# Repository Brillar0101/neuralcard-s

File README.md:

# NeuralCard

A business card that runs a neural network.

> This is the sponsorship build, a fork of
> [NeuralCard](https://github.com/Brillar0101/NeuralCard) prepared for assembly by
> PCBWay. The BOM has been rewritten from JLCPCB and LCSC part codes into
> manufacturer part numbers PCBWay can quote, with approved alternates where a swap
> is safe and do-not-substitute rules where it is not. Every part in the schematic
> and the board now carries `Alt MPN`, `Alt Mfr`, and `Sourcing` fields alongside
> the existing MPN. See [`docs/SOURCING.md`](docs/SOURCING.md) for the reasoning and
> [`fab/BOM_PCBWay.csv`](fab/BOM_PCBWay.csv) for the order-ready BOM. No copper
> changed, and DRC and ERC still pass clean.

It is a credit-card-sized PCB, 85.6 by 54 mm, carrying an ESP32-S3, a 6-axis
IMU, and 24 LEDs laid out as the network it actually runs: 6 input neurons,
8 hidden, 10 output. You hold the card, draw a digit in the air, and the LEDs
light with the real activations as inference runs. Brightest output neuron
wins.

The front artwork is the network diagram. The synapse lines are drawn at three
stroke weights, the way a trained model's weights differ. There is also an NFC
tag with a coil antenna etched into the copper, so tapping a phone opens
[princetekki.com/card](https://www.princetekki.com/card) and offers a vCard.
That works with a dead battery, or no battery at all, because the phone's own
field powers the tag.

## Repository layout

| Path | What's in it |
|---|---|
| `hardware/` | KiCad 10 project: schematic, board, custom symbol and footprint libraries, 3D models |
| `fab/` | Manufacturing outputs: gerber zip, drill files, pick-and-place, and two BOMs: `BOM_PCBWay.csv` (MPN-based, for this build) and `BOM_JLCPCB.csv` (upstream, LCSC codes) |
| `firmware/` | ESP-IDF project. Charlieplex driver, IMU driver, gesture recorder. Builds today. |
| `docs/` | Design rationale, component sourcing, datasheet findings, DRC history, audits, FAQ |
| `render/` | The board renders used above |
| `CHANGELOG.md` | Revision history, newest first |

Start with [`docs/DESIGN.md`](docs/DESIGN.md) for why the board is shaped the
way it is, [`docs/FAQ.md`](docs/FAQ.md) for the questions people actually ask,
and [`docs/drc/README.md`](docs/drc/README.md) for the verification trail.

## Hardware

An ESP32-S3-WROOM-1-N8R2 does the thinking and runs the inference. An
LSM6DS3TR-C accelerometer and gyro sits on I2C, and its six axes map one to one
onto the six input neurons. The 24 red LEDs are charlieplexed across 6 GPIO
with software PWM for the glow.

For the business-card half there is an ST25DV04K dynamic NFC tag with a 9-turn
coil in the copper, tuned by a single external cap (C12) against the chip's
internal capacitance.

USB-C arrived in v2.3. The S3 has native USB, so a plain cable flashes the
board and gives a serial console without an adapter. A USBLC6-2SC6 protects the
data pair.

Power comes from either a CR2032 through a real slide switch (SW3) or USB 5 V
through an ME6211 LDO. A P-FET (Q1) disconnects the cell whenever USB is
present, so the board can never try to charge a cell that is not rechargeable.

Two layers, ground poured on both sides and stitched. Every net is one
connected cluster.

## How it's wired

Power first. Two sources that can never fight each other.

```mermaid
flowchart LR
    USB["USB-C · J2<br/>5 V VBUS"] --> LDO["U3 · ME6211<br/>3.3 V LDO"]
    BT1["BT1<br/>CR2032 · 3.0 V"] -->|VBAT| SW3{{"SW3 · MSK12C02<br/>SPDT slide"}}
    SW3 -->|"ON"| Q1{{"Q1 · AO3401A<br/>P-FET isolation"}}
    SW3 -.->|"OFF"| NC(["open throw"])
    LDO --> RAIL[["+3V3 rail"]]
    LDO -.->|"VBUS present<br/>gates the cell off"| Q1
    Q1 --> RAIL
    RAIL --> U1["ESP32-S3"]
    RAIL --> U2["LSM6DS3TR-C"]
    RAIL --> U4["ST25DV04K"]
    RAIL --> LEDS["24 LEDs<br/>charlieplexed"]

    classDef src fill:#F0AB00,stroke:#795600,color:#151515
    classDef sw fill:#0066CC,stroke:#003366,color:#FFFFFF
    classDef rail fill:#009596,stroke:#005F60,color:#FFFFFF
    classDef load fill:#F0F0F0,stroke:#8A8D90,color:#151515
    classDef off fill:#FFFFFF,stroke:#C9190B,color:#C9190B,stroke-dasharray:4 3
    class USB,BT1 src
    class SW3,Q1,LDO sw
    class RAIL rail
    class U1,U2,U4,LEDS load
    class NC off
```

Then data. USB-C carries both power and programming. NFC is independent of
both and needs no power of its own.

```mermaid
flowchart LR
    HOST(["laptop"]) -->|"USB-C · D+/D-"| ESD["U5 · USBLC6<br/>ESD array"]
    ESD -->|"native USB-Serial-JTAG"| U1["ESP32-S3"]
    U1 <-->|I2C| U2["IMU"]
    U1 <-->|I2C| U4["NFC tag"]
    U2 -.->|"motion interrupt"| U1
    U4 -.->|"field-detect GPO"| U1
    PHONE(["phone"]) -.->|"13.56 MHz field<br/>powers the tag"| U4
    U1 --> LEDS["24 LEDs"]

    classDef ext fill:#F0AB00,stroke:#795600,color:#151515
    classDef chip fill:#0066CC,stroke:#003366,color:#FFFFFF
    classDef out fill:#3E8635,stroke:#1F4D19,color:#FFFFFF
    class HOST,PHONE ext
    class ESD,U1,U2,U4 chip
    class LEDS out
```

And inference. The six IMU axes feed the six input neurons, and the LEDs at
each node light with the real activations as the network runs.

```mermaid
flowchart LR
    IMU["LSM6DS3TR-C<br/>ax ay az · gx gy gz"] --> IN["INPUT<br/><b>6 neurons</b>"]
    IN --> HID["HIDDEN<br/><b>8 neurons</b>"]
    HID --> OUT["OUTPUT<br/><b>10 neurons</b><br/>digits 0-9"]
    OUT --> GUESS(["brightest neuron<br/>= the guess"])

    classDef sensor fill:#F0AB00,stroke:#795600,color:#151515
    classDef layer fill:#0066CC,stroke:#003366,color:#FFFFFF
    classDef out fill:#5752D1,stroke:#2A265F,color:#FFFFFF
    classDef result fill:#3E8635,stroke:#1F4D19,color:#FFFFFF
    class IMU sensor
    class IN,HID layer
    class OUT out
    class GUESS result
```

All 24 LEDs run from 6 GPIO by charlieplexing. That is why there are 6
current-limiting resistors rather than 24, and why the display works on a coin
cell at all: only one LED is ever actually lit.

## Firmware

`firmware/` is an ESP-IDF project that builds today. It has the charlieplex
driver, with the LED-to-pin mapping extracted from the board netlist rather
than guessed, the LSM6DS3 driver, and a motion-triggered gesture recorder that
prints labelled CSV over the USB-C console. That recorder is how you build a
training set.

```
cd firmware && idf.py set-target esp32s3 && idf.py build && idf.py flash monitor
```

The neural network itself is deliberately not in the repo yet: it has to be
trained on gestures recorded from real hands, which needs assembled boards.
See [`firmware/README.md`](firmware/README.md).

## Ordering

Everything a fab needs is in `fab/`: `NeuralCard_gerbers.zip` (gerbers +
drill), `NeuralCard-cpl.csv` (placements), and a BOM. Use
`BOM_PCBWay.csv` for this build, which carries manufacturer part numbers,
approved alternates, and per-line substitution rules. `BOM_JLCPCB.csv` is the
upstream file and is keyed to LCSC codes instead.

Build spec: 2 layers, 1.6 mm thickness, green soldermask, HASL. That is the
cheap prototype configuration, currently about $2 for five boards.

Two finish options are worth knowing about if you ever make a batch to hand
out. At 0.8 mm the board feels like a card instead of a circuit board. With
ENIG, the hairline under the name comes out gold, since it is a mask opening
over the ground pour and plates with whatever finish you pick. Both cost more.
Neither changes the gerbers, so they are order-time choices.

**Two build routes:**

Hand assembly means ordering bare boards plus a solder-paste stencil and
buying parts from LCSC. It is the cheapest route, and the stencil is what makes
the LGA-14 IMU tractable with hot air.

Factory assembly means turnkey PCBA on both sides. It adds roughly $100 of fixed
setup and feeder cost at a typical prototype house, so it only pays off around 30
boards or more. This build is being assembled by PCBWay under sponsorship, so see
[`docs/SOURCING.md`](docs/SOURCING.md) for how the parts are actually bought.

Two BOM notes. C12, the NFC tuning cap, ships as 68 pF and should be retuned
against the coil once it exists. Read range is the practical test. The NFC chip
is ST25DV04KC-IE6S3, which is the active part. The older ST25DV04K-IER6S3 is
marked not recommended for new designs but is still widely stocked, and it is
listed as the approved fallback: same package, same pinout, same function.

## Status

The hardware is done and verified at v2.3.1: DRC reports 0 violations and 0
unconnected, ERC is clean, every net is a single connected cluster, and the
footprints have been checked against manufacturer datasheets. It has never been
fabricated. These files would produce the first physical boards.

The firmware scaffold builds. Drivers and gesture capture work. The trained
model is the remaining piece, and it needs assembled boards before it can
exist.

So today the card is a very elaborate NFC business card, and that part works
the moment the tag is programmed.

## License

CERN-OHL-P v2. See [LICENSE](LICENSE). Do whatever you want with it,
attribution appreciated.

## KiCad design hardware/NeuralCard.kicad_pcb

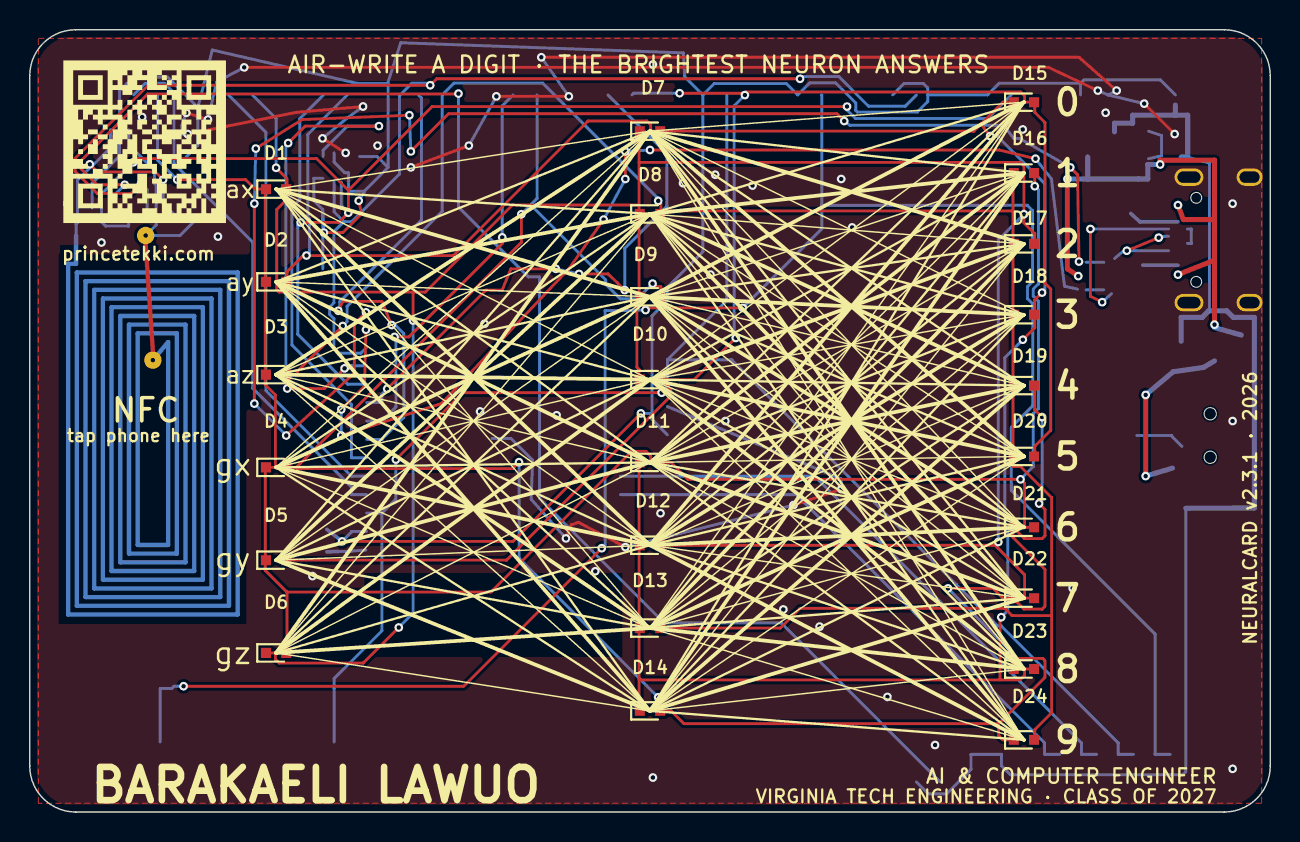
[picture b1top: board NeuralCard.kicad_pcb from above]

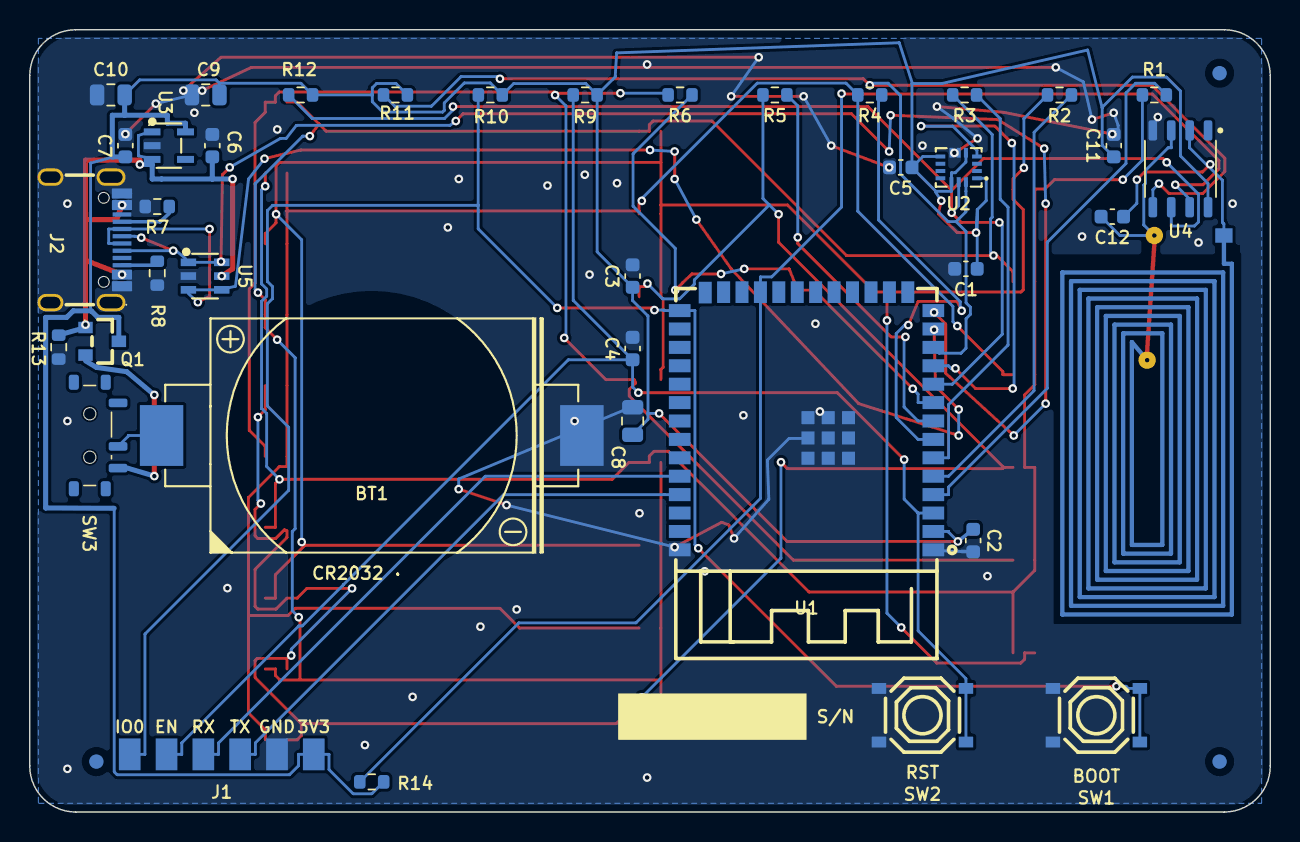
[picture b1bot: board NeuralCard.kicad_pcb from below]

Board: 2 copper layers, 85.6 x 54.0 mm, 66 parts (42 on the bottom side), 31 nets.

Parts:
ANT1: NFC_COIL; NFC_Antenna_13x24
BT1: BAT-TH_CR2032-BS-6-1
C1, C2, C3, C4, C5, C11, C12: C_0603_1608Metric
C6, C7: 1uF; C_0603_1608Metric
C8, C9, C10: C_0805_2012Metric
D1, D2, D3, D4, D5, D6, D7, D8, D9, D10, D11, D12, D13, D14, D15, D16, D17, D18, D19, D20, D21, D22, D23, D24: LED-SMD_L1.6-W0.8-R-RD
FID1, FID2, FID3: Fiducial_1mm_Mask2mm
J1: ProgPads; ProgPads_1x6
J2: TYPE-C-31-M-12; USB-C_SMD-TYPE-C-31-M-12_1
Q1: AO3401A; SOT-23_L2.9-W1.3-P1.90-LS2.4-BR
R1, R2, R3, R4, R5, R6, R9, R10, R11, R12, R14: R_0603_1608Metric
R7, R8: 5.1k; R_0603_1608Metric
R13: 100k; R_0603_1608Metric
SW1, SW2: SW-SMD_4P-L5.1-W5.1-P3.70-LS6.5-TL_H1.5
SW3: SW_SPDT_Shouhan_MSK12C02
U1: WIRELM-SMD_ESP32-S3-WROOM-1
U2: LGA-14_L3.0-W2.5-P0.50-TL
U3: ME6211C33M5G-N; SOT-23-5_L3.0-W1.7-P0.95-LS2.8-BL
U4: SO-8_L4.9-W3.9-P1.27-LS5.9-BL
U5: USBLC6-2SC6; SOT-23-6_L2.9-W1.6-P0.95-LS2.8-BL

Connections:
+3V3: C1.1, C2.1, C3.1, C5.1, C7.1, C8.1, C9.1, C10.1, C11.1, J1.1, Q1.3, R9.1, R10.1, R11.1, R12.1, R14.1, U1.2, U2.1, U2.5, U2.8, U2.12, U3.5, U4.8
CC1: J2.A5, R7.1
CC2: J2.B5, R8.1
CHX1: R1.1, U1.4
CHX2: R2.1, U1.5
CHX3: R3.1, U1.6
CHX4: R4.1, U1.7
CHX5: R5.1, U1.8
CHX6: R6.1, U1.9
CP1: D1.2, D2.2, D3.2, D4.2, D5.2, D6.1, D11.1, D16.1, D21.1, R1.2
CP2: D1.1, D6.2, D7.2, D8.2, D9.2, D10.2, D12.1, D17.1, D22.1, R2.2
CP3: D2.1, D7.1, D11.2, D12.2, D13.2, D14.2, D15.2, D18.1, D23.1, R3.2
CP4: D3.1, D8.1, D13.1, D16.2, D17.2, D18.2, D19.2, D20.2, D24.1, R4.2
CP5: D4.1, D9.1, D14.1, D19.1, D21.2, D22.2, D23.2, D24.2, R5.2
CP6: D5.1, D10.1, D15.1, D20.1, R6.2
EN: C4.1, J1.5, R9.2, SW2.1, SW2.3, U1.3
GND: BT1.2, C1.2, C2.2, C3.2, C4.2, C5.2, C6.2, C7.2, C8.2, C9.2, C10.2, C11.2, J1.2, J2.1, J2.2, J2.3, J2.4, J2.A1B12, J2.B1A12, R7.2, R8.2, R13.2, SW1.2, SW1.4, SW2.2, SW2.4, U1.1, U1.40, U1.41, U2.6, U2.7, U3.2, U4.4, U5.2
IMU_INT: U1.11, U2.4
IO0: J1.6, R10.2, SW1.1, SW1.3, U1.27
NFC_ANT_A: ANT1.1, C12.1, U4.2
NFC_ANT_B: ANT1.2, C12.2, U4.3
NFC_GPO: R14.2, U1.23, U4.7
RXD: J1.4, U1.36
SCL: R12.2, U1.10, U2.13, U4.6
SDA: R11.2, U1.12, U2.14, U4.5
TXD: J1.3, U1.37
USB_DM: J2.A7, J2.B7, U1.13, U5.3, U5.4
USB_DP: J2.A6, J2.B6, U1.14, U5.1, U5.6
VBAT: BT1.1, SW3.2
VBAT_SW: Q1.2, SW3.3
VBUS: C6.1, J2.A4B9, J2.B4A9, Q1.1, R13.1, U3.1, U3.3, U5.5

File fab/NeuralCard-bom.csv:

Comment,Designator,Footprint,LCSC Part #
"ESP32-S3-WROOM-1-N8R2 (C2913204 is the N8R2 variant; pick an N16R8 ID at order if the bigger memory is wanted)",U1,WIRELM-SMD_ESP32-S3-WROOM-1,C2913204
"LSM6DS3TR-C IMU (LGA-14 0.5mm pitch - stencil + hot plate strongly advised)",U2,LGA-14_L3.0-W2.5-P0.50-TL,C967633
"ME6211C33M5G-N 3.3V 500mA LDO (VBUS -> +3V3)",U3,SOT-23-5_L3.0-W1.7-P0.95-LS2.8-BL,C82942
"ST25DV04K-IER6S3 NFC tag (subst for ST25DV04KC-IE6S3/C3304276 which is near end-of-stock; same SO-8, same pinout, same I2C/NFC function)",U4,SO-8_L4.9-W3.9-P1.27-LS5.9-BL,C155601
"USBLC6-2SC6 ESD array on USB_DP/USB_DM",U5,SOT-23-6_L2.9-W1.6-P0.95-LS2.8-BL,C7519
"AO3401A P-FET (isolates coin cell while VBUS present)",Q1,SOT-23_L2.9-W1.3-P1.90-LS2.4-BR,C15127
"CR2032-BS-6-1 holder (battery itself not included - buy a CR2032 cell separately)",BT1,BAT-TH_CR2032-BS-6-1,C70377
"USB-C receptacle TYPE-C-31-M-12 16P (power + USB2 data)",J2,USB-C_SMD-TYPE-C-31-M-12_1,C165948
"TS-1187A tact (BOOT)",SW1,SW-SMD_4P-L5.1-W5.1-P3.70-LS6.5-TL_H1.5,C318884
"TS-1187A tact (RESET)",SW2,SW-SMD_4P-L5.1-W5.1-P3.70-LS6.5-TL_H1.5,C318884
"SPDT slide switch MSK12C02 (8x2.8mm, right-angle, 4 shield tabs + 2x0.85mm NPTH) - POWER on/off, in series with coin cell + terminal",SW3,SW_SPDT_Shouhan_MSK12C02,C431540
"100nF 0603 X7R 50V",C1,C0603,C14663
"100nF 0603 X7R 50V",C2,C0603,C14663
"100nF 0603 X7R 50V",C3,C0603,C14663
"100nF 0603 X7R 50V",C4,C0603,C14663
"100nF 0603 X7R 50V",C5,C0603,C14663
"1uF 0603 X5R 50V (LDO VIN; subst for C15849 which showed zero assembly stock)",C6,C0603,C128624
"1uF 0603 X5R 50V (LDO VOUT; subst for C15849 which showed zero assembly stock)",C7,C0603,C128624
"10uF 0805 X5R 25V",C8,C0805,C15850
"22uF 0805 X5R 25V",C9,C0805,C45783
"22uF 0805 X5R 25V (schematic corrected to 22uF in v2.3; consider 1206/100uF next rev for extra WiFi-burst headroom)",C10,C0805,C45783
"100nF 0603 X7R 50V",C11,C0603,C14663
"68pF C0G 50V 0603 (NFC tuning; design target 62pF, 56-68pF window - verify with VNA after assembly and swap if needed)",C12,C0603,C28262
"Red LED 0603 KT-0603R (front face, 24x)",D1,LED-SMD_L1.6-W0.8-R-RD,C2286
"Red LED 0603 KT-0603R",D2,LED-SMD_L1.6-W0.8-R-RD,C2286
"Red LED 0603 KT-0603R",D3,LED-SMD_L1.6-W0.8-R-RD,C2286
"Red LED 0603 KT-0603R",D4,LED-SMD_L1.6-W0.8-R-RD,C2286
"Red LED 0603 KT-0603R",D5,LED-SMD_L1.6-W0.8-R-RD,C2286
"Red LED 0603 KT-0603R",D6,LED-SMD_L1.6-W0.8-R-RD,C2286
"Red LED 0603 KT-0603R",D7,LED-SMD_L1.6-W0.8-R-RD,C2286
"Red LED 0603 KT-0603R",D8,LED-SMD_L1.6-W0.8-R-RD,C2286
"Red LED 0603 KT-0603R",D9,LED-SMD_L1.6-W0.8-R-RD,C2286
"Red LED 0603 KT-0603R",D10,LED-SMD_L1.6-W0.8-R-RD,C2286
"Red LED 0603 KT-0603R",D11,LED-SMD_L1.6-W0.8-R-RD,C2286
"Red LED 0603 KT-0603R",D12,LED-SMD_L1.6-W0.8-R-RD,C2286
"Red LED 0603 KT-0603R",D13,LED-SMD_L1.6-W0.8-R-RD,C2286
"Red LED 0603 KT-0603R",D14,LED-SMD_L1.6-W0.8-R-RD,C2286
"Red LED 0603 KT-0603R",D15,LED-SMD_L1.6-W0.8-R-RD,C2286
"Red LED 0603 KT-0603R",D16,LED-SMD_L1.6-W0.8-R-RD,C2286
"Red LED 0603 KT-0603R",D17,LED-SMD_L1.6-W0.8-R-RD,C2286
"Red LED 0603 KT-0603R",D18,LED-SMD_L1.6-W0.8-R-RD,C2286
"Red LED 0603 KT-0603R",D19,LED-SMD_L1.6-W0.8-R-RD,C2286
"Red LED 0603 KT-0603R",D20,LED-SMD_L1.6-W0.8-R-RD,C2286
"Red LED 0603 KT-0603R",D21,LED-SMD_L1.6-W0.8-R-RD,C2286
"Red LED 0603 KT-0603R",D22,LED-SMD_L1.6-W0.8-R-RD,C2286
"Red LED 0603 KT-0603R",D23,LED-SMD_L1.6-W0.8-R-RD,C2286
"Red LED 0603 KT-0603R",D24,LED-SMD_L1.6-W0.8-R-RD,C2286
"220R 0603 (charlieplex)",R1,R0603,C22962
"220R 0603 (charlieplex)",R2,R0603,C22962
"220R 0603 (charlieplex)",R3,R0603,C22962
"220R 0603 (charlieplex)",R4,R0603,C22962
"220R 0603 (charlieplex)",R5,R0603,C22962
"220R 0603 (charlieplex)",R6,R0603,C22962
"5.1k 0603 (USB-C CC1 pulldown, Rd)",R7,R0603,C23186
"5.1k 0603 (USB-C CC2 pulldown, Rd)",R8,R0603,C23186
"10k 0603 (EN pull-up)",R9,R0603,C25804
"10k 0603 (IO0/BOOT pull-up)",R10,R0603,C25804
"4.7k 0603 (I2C SDA pull-up)",R11,R0603,C23162
"4.7k 0603 (I2C SCL pull-up)",R12,R0603,C23162
"100k 0603 (Q1 gate pulldown)",R13,R0603,C25803
"100k 0603 (NFC_GPO pull)",R14,R0603,C25803
